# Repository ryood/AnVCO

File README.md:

AnVCO

Analog VCO
  Sawtooth
  Triangle
  Square

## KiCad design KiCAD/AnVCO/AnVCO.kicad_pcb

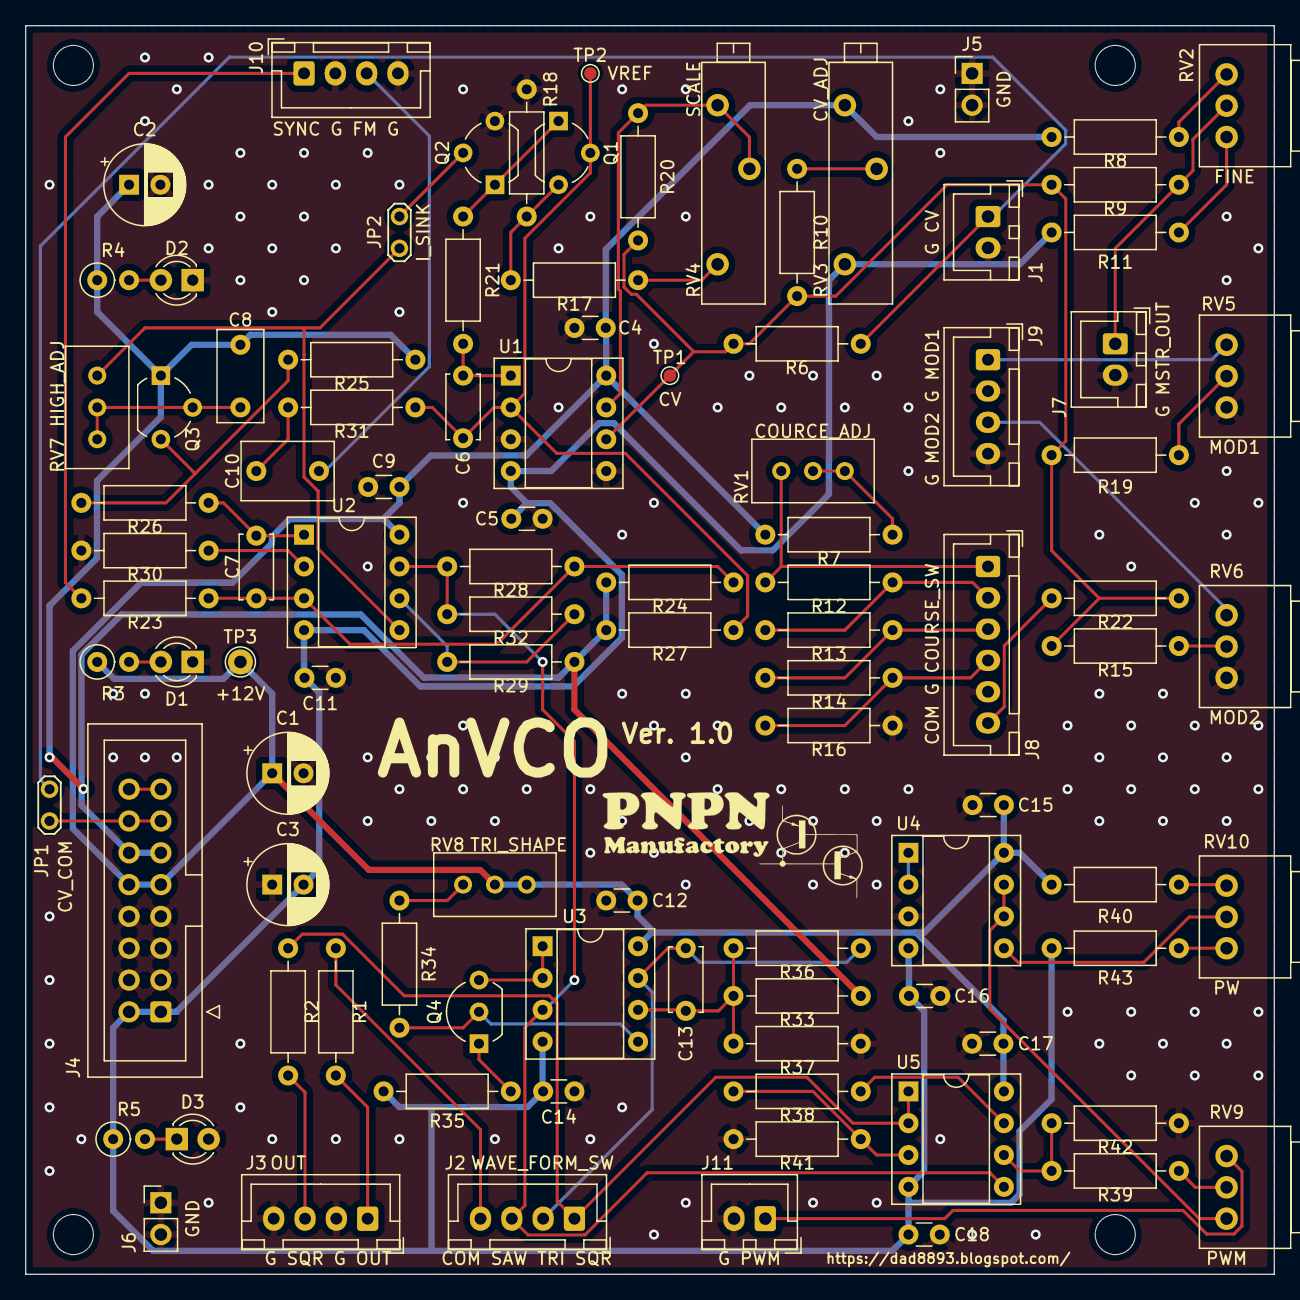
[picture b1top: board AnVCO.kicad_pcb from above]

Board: 2 copper layers, 99.7 x 99.7 mm, 103 parts (0 on the bottom side), 63 nets.

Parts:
C1, C2, C3: 100uF; CP_Radial_D6.3mm_P2.50mm
C4, C5, C9, C11: 0.1u; C_Disc_D3.0mm_W1.6mm_P2.50mm
C6, C7: 100p; C_Disc_D5.0mm_W2.5mm_P5.00mm
C8: 0.01uF; C_Rect_L7.2mm_W3.5mm_P5.00mm_FKS2_FKP2_MKS2_MKP2
C10: 1u; C_Rect_L7.2mm_W4.5mm_P5.00mm_FKS2_FKP2_MKS2_MKP2
C12, C14, C15, C16, C17, C18: 0.1uF; C_Disc_D3.0mm_W1.6mm_P2.50mm
C13: 68pF; C_Disc_D5.0mm_W2.5mm_P5.00mm
D1: RED; LED_D3.0mm
D2: GREEN; LED_D3.0mm
D3: BLUE; LED_D3.0mm
H1, H2, H3, H4: MountingHole; MountingHole_3.2mm_M3
J1: CV; JST_XH_B2B-XH-A_1x02_P2.50mm_Vertical
J2: SW_WaveForm; JST_XH_B4B-XH-A_1x04_P2.50mm_Vertical
J3: OUT; JST_XH_B4B-XH-A_1x04_P2.50mm_Vertical
J4: ERK_PWR; IDC-Header_2x08_P2.54mm_Vertical
J5, J6: TP_GND; PinHeader_1x02_P2.54mm_Vertical
J7: MSTR_OUT; JST_XH_B2B-XH-A_1x02_P2.50mm_Vertical
J8: COURSE_SW; JST_XH_B6B-XH-A_1x06_P2.50mm_Vertical
J9: MOD; JST_XH_B4B-XH-A_1x04_P2.50mm_Vertical
J10: Sync&FM; JST_XH_B4B-XH-A_1x04_P2.50mm_Vertical
J11: PWM; JST_XH_B2B-XH-A_1x02_P2.50mm_Vertical
JP1: CV_THRU; TestPoint_2Pads_Pitch2.54mm_Drill0.8mm
JP2: TP_I_SINK; TestPoint_2Pads_Pitch2.54mm_Drill0.8mm
Q1, Q2: 2SC1815; TO-92_Wide
Q3: 2SA1015; TO-92_Wide
Q4: 2SC1815; TO-92_Inline_Wide
R1, R2, R12, R13, R14, R16, R21: 1k; R_Axial_DIN0207_L6.3mm_D2.5mm_P10.16mm_Horizontal
R3, R5: 4.7k; R_Axial_DIN0207_L6.3mm_D2.5mm_P2.54mm_Vertical
R4: 1k; R_Axial_DIN0207_L6.3mm_D2.5mm_P2.54mm_Vertical
R6, R9, R15, R19, R20, R22, R37: 470k; R_Axial_DIN0207_L6.3mm_D2.5mm_P10.16mm_Horizontal
R7: 5k; R_Axial_DIN0207_L6.3mm_D2.5mm_P10.16mm_Horizontal
R8, R11: 270k; R_Axial_DIN0207_L6.3mm_D2.5mm_P10.16mm_Horizontal
R10, R24, R27, R28, R29, R36: 100k; R_Axial_DIN0207_L6.3mm_D2.5mm_P10.16mm_Horizontal
R17, R30, R34, R35: 10k; R_Axial_DIN0207_L6.3mm_D2.5mm_P10.16mm_Horizontal
R18: 1k tempco; R_Axial_DIN0207_L6.3mm_D2.5mm_P10.16mm_Horizontal
R23: 22k(C&T); R_Axial_DIN0207_L6.3mm_D2.5mm_P10.16mm_Horizontal
R25: 150; R_Axial_DIN0207_L6.3mm_D2.5mm_P10.16mm_Horizontal
R26: 680; R_Axial_DIN0207_L6.3mm_D2.5mm_P10.16mm_Horizontal
R31: 100k(C&T); R_Axial_DIN0207_L6.3mm_D2.5mm_P10.16mm_Horizontal
R32: 120k; R_Axial_DIN0207_L6.3mm_D2.5mm_P10.16mm_Horizontal
R33: 150k; R_Axial_DIN0207_L6.3mm_D2.5mm_P10.16mm_Horizontal
R38: 2.2k; R_Axial_DIN0207_L6.3mm_D2.5mm_P10.16mm_Horizontal
R39: 220k; R_Axial_DIN0207_L6.3mm_D2.5mm_P10.16mm_Horizontal
R40, R43: 68k; R_Axial_DIN0207_L6.3mm_D2.5mm_P10.16mm_Horizontal
R41: 1.8k; R_Axial_DIN0207_L6.3mm_D2.5mm_P10.16mm_Horizontal
R42: 2.2M; R_Axial_DIN0207_L6.3mm_D2.5mm_P10.16mm_Horizontal
RV1, RV7, RV8: 5k; Potentiometer_Bourns_3296W_Vertical
RV2: 50k/B; Potentiometer_Alps_RK097_Single_Horizontal
RV3: 10k/Multi; Potentiometer_Bourns_3006P_Horizontal
RV4: 50k/Multi; Potentiometer_Bourns_3006P_Horizontal
RV5, RV6: 50k/A; Potentiometer_Alps_RK097_Single_Horizontal
RV9: 50kA; Potentiometer_Alps_RK097_Single_Horizontal
RV10: 50kB; Potentiometer_Alps_RK097_Single_Horizontal
TP1: TP_CV; TestPoint_Pad_D1.0mm
TP2: TP_VREF; TestPoint_Pad_D1.0mm
TP3: TP_+12V; TestPoint_THTPad_D2.0mm_Drill1.0mm
U1, U2, U3, U4, U5: TL072; DIP-8_W7.62mm_Socket

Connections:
+5V: C2.1, C8.2, J4.11, J4.12, Q3.1, R4.1, R24.1, R25.1, R27.1, R29.2, R33.1
+12V: C1.1, C4.2, C9.2, C12.2, C15.2, C17.2, J4.9, J4.10, R3.1, R7.1, R8.1, R40.1, RV3.3, RV8.1, RV8.2, TP3.1, U1.8, U2.8, U3.8, U4.8, U5.8
-12V: C3.2, C5.2, C11.2, C14.2, C16.1, C18.1, J4.1, J4.2, R5.1, R11.2, R35.2, R43.2, RV3.1, U1.4, U2.4, U3.4, U4.4, U5.4
/Antilog_NPNO/CV: J1.1, JP1.2, R6.2
/Antilog_NPNO/I_SINK: JP2.1, RV7.3, U2.5
/Antilog_NPNO/VREF: C6.2, Q1.2, R27.2, R31.1, TP2.1, U1.2
/GATE: J4.15, J4.16
/Saw2Sqr/SAW_IN: J2.3, R28.2, R32.2, U2.7, U3.3, U5.5
/Saw2Sqr/SQR_OUT: J2.1, R2.2, U5.1, U5.2
/Saw2Tri/TRI_OUT: C13.1, J2.2, R36.2, U3.7
GND: C1.2, C2.2, C3.1, C4.1, C5.1, C9.1, C11.1, C12.1, C14.1, C15.1, C16.2, C17.1, C18.2, D1.1, D2.1, D3.2, J1.2, J3.2, J3.4, J4.3, J4.4, J4.5, J4.6, J4.7, J4.8, J5.1, J5.2, J6.1, J6.2, J7.2, J8.5, J9.2, J9.4, J10.2, J10.4, J11.2, Q2.3, R16.2, R18.2, R30.2, R37.2, R41.2, R42.2, RV5.1, RV6.1, U1.3, U1.5, U4.3
unnamed: C6.1, R21.2, U1.1
unnamed: C7.1, R23.1, R24.2, R28.1, U2.3
unnamed: C7.2, R26.1, U2.1
unnamed: C8.1, Q3.2, RV7.1, RV7.2
unnamed: C10.1, R31.2
unnamed: C10.2, J10.3
unnamed: C13.2, R33.2, R36.1, R37.1, U3.6
unnamed: D1.2, R3.2
unnamed: D2.2, R4.2
unnamed: D3.1, R5.2
unnamed: J2.4, R1.2
unnamed: J3.1, R1.1
unnamed: J3.3, R2.1
unnamed: J4.13, J4.14, JP1.1
unnamed: J7.1, R9.2, RV2.2
unnamed: J8.1, R12.1, RV1.1
unnamed: J8.2, R12.2, R13.1
unnamed: J8.3, R13.2, R14.1
unnamed: J8.4, R14.2, R16.1
unnamed: J8.6, R15.2
unnamed: J9.1, RV5.3
unnamed: J9.3, RV6.3
unnamed: J10.1, R23.2
unnamed: J11.1, RV9.3
unnamed: JP2.2, Q2.2
unnamed: Q1.1, Q2.1, R21.1
unnamed: Q1.3, R17.1, R18.1
unnamed: Q3.3, R25.2, R26.2
unnamed: Q4.1, R35.1
unnamed: Q4.2, R34.2, U3.5
unnamed: Q4.3, U3.1, U3.2
unnamed: R7.2, RV1.2, RV1.3
unnamed: R8.2, RV2.3
unnamed: R10.1, RV3.2
unnamed: R6.1, R9.1, R10.2, R15.1, R19.1, R20.2, R22.1, TP1.1, U1.6
unnamed: R11.1, RV2.1
unnamed: R17.2, RV4.1
unnamed: R19.2, RV5.2
unnamed: R20.1, RV4.2, RV4.3, U1.7
unnamed: R22.2, RV6.2
unnamed: R29.1, R32.1, U2.6
unnamed: R30.1, U2.2
unnamed: R34.1, RV8.3
unnamed: R38.1, R41.1, U5.3
unnamed: R38.2, U5.7
unnamed: R39.1, R42.1, U5.6
unnamed: R39.2, RV9.2
unnamed: R40.2, RV10.3
unnamed: R43.1, RV10.1
unnamed: RV9.1, U4.6, U4.7
unnamed: RV10.2, U4.5
unnamed: U4.1, U4.2

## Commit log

2022-01-16 KiCAD files
2022-02-02 Before wiring
2022-03-22 Ver.1.0
